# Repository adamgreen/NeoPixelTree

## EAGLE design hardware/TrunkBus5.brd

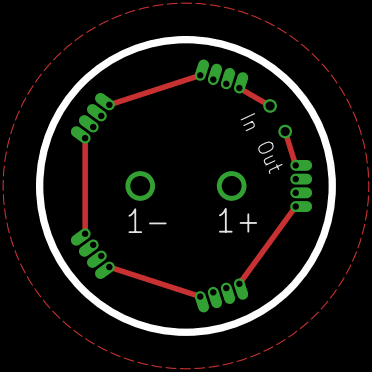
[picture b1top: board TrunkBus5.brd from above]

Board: 2 copper layers, 16.3 x 16.3 mm, 8 parts (0 on the bottom side), 8 nets.

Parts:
E$1: NEOPIXEL_TRUNK_2WIRE
E$5, E$6, E$7, E$8, E$10: NEOPIXEL_BRANCH_4WIRE
E$12, E$13: NEOPIXEL_26AWG_HOLE

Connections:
5V: E$1.P$1, E$5.P$1, E$6.P$1, E$7.P$1, E$8.P$1, E$10.P$1
GND: E$1.P$2, E$5.P$2, E$6.P$2, E$7.P$2, E$8.P$2, E$10.P$2
S$1: E$8.P$4, E$10.P$3
S$2: E$10.P$4, E$12.P$1
S$4: E$5.P$3, E$13.P$1
S$7: E$5.P$4, E$6.P$3
S$8: E$6.P$4, E$7.P$3
S$10: E$7.P$4, E$8.P$3

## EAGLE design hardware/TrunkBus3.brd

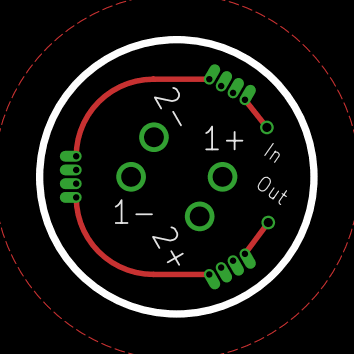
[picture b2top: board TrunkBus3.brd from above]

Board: 2 copper layers, 15.2 x 15.2 mm, 7 parts (0 on the bottom side), 6 nets.

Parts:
E$1, E$11: NEOPIXEL_TRUNK_2WIRE
E$2, E$6, E$8: NEOPIXEL_BRANCH_4WIRE
E$12, E$13: NEOPIXEL_26AWG_HOLE

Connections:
5V: E$1.P$1, E$2.P$1, E$6.P$1, E$8.P$1, E$11.P$1
GND: E$1.P$2, E$2.P$2, E$6.P$2, E$8.P$2, E$11.P$2
S$1: E$8.P$4, E$12.P$1
S$2: E$2.P$3, E$13.P$1
S$4: E$2.P$4, E$6.P$3
S$8: E$6.P$4, E$8.P$3

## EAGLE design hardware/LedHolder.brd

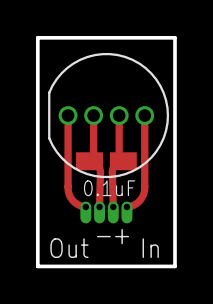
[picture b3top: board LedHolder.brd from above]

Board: 2 copper layers, 7.6 x 12.7 mm, 3 parts (0 on the bottom side), 4 nets.

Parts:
E$1: NEOPIXEL_5MM_TH
E$2: NEOPIXEL_BRANCH_4WIRE
E$3: 0.1uF; R0805W

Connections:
S$1: E$1.GROUND, E$2.P$1, E$3.1
S$2: E$1.5V, E$2.P$2, E$3.2
S$3: E$1.DATA_OUT, E$2.P$3
S$4: E$1.DATA_IN, E$2.P$4

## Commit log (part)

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2016-03-26 Add gcc4mbed as a submodule
    Using the working branch for now.
2016-03-27 GPDMA/SPI based updates of NeoPixels now working
    This commit is a checkpoint where the code is now able to use the
    GPDMA/SPI peripherals on the LPC17xx to automatically send out the
    required single wire waveform for the WS2812 based NeoPixels. The CPU
    is only used to convert the desired LED RGB values to a bitstream that
    can be sent out over the SPI MOSI pin to generate the expected WS2812
    waveform. This saves CPU cycles to be used for running animations.
2016-03-27 I don't need interlocked operations for this driver
    A previous implementation that I was working on needed to increment the
    frame counter in an interlocked fashion but this one doesn't.
2016-03-27 Remove some old debug code from main.cpp
    I had some leftover debug code in main.cpp where I was verifying that
    both front buffers were being updated correctly when client doesn't
    provide a new frame on very frame flip.
2016-03-27 Initial animation support
    This is the beginning of the various animations I want to try with this
    NeoPixel configuration.
    This commit includes:
    * I updated NeoPixel::set() method to take the length of the pPixel
    array passed in so that it can be verified against the m_ledCount
    that was set at construction time.
2016-03-27 Add twinkling animation
    I added an IPixelUpdate interface which the already existing Animation
    class now implements and so does the new TwinkleAnimation class. The
    main program then just maintains a IPixelUpdate pointer to the current
    animation engine and calls its updatePixels() method on each iteration
    through its main loop.
2016-03-27 Make animations templated on pixel count
    The animation classes no longer need to dynamically allocate pixel
    arrays. Now they take the pixel count as a template parameter and
    define an array within the class which is big enough to hold the
    pixels.
2016-03-29 Add back buffer support
    Previously the main thread would wait for the current front buffer to
    be sent and then it would fill that front buffer in while the other was
    being sent. This caused the CPU on average to wait half of a frame
    period each time it called NeoPixel::set().
    This new version has the main thread just filling in a separate
    back buffer. That back buffer will then be copied into the next front
2016-03-29 Add candle flicker animation
    This is the start of an animation that makes the LEDs flicker similar
    to how store bot LED candles flicker. The following webpage created by
    @cpldcpu provided a lot of inspiration for this animation:
    https://cpldcpu.wordpress.com/2016/01/05/reverse-engineering-a-real-candle/
    I also cleaned up some trailing whitespace in my logarithm table.
2016-04-01 Add some blue-white patterns as well
2016-04-01 Add schematic for current prototype
    This commit adds the Eagle schematic for the current 5 LED prototype
    that I am currently testing.
2016-04-02 Photos of tree prototype
2016-04-02 Add BSS138 N-Channel MOSFET documentation
2016-04-02 Initial README commit
2016-04-03 Fix error in README
    I had added a line break into the middle of a link by mistake.
2016-04-03 SPI bit layout comments were incorrect
    They were incorrectly indicating that a high bit to be sent to the
    WS2812 would be represented with 8 high pixels rather than the actual
    7 used in the driver.
2016-04-08 Add images
    The first is a clip from page 4 of the WS2812 LED driver datasheet. It
    shows the bit timings for the WS2812 serial protocol.
    The rest are hand drawn timing diagrams for my SPI implementation of
    the WS2812 serial protocol.
2016-04-08 Update README
    Added notes describing how I use SPI to generate WS2812 bit timings.
2016-04-08 Fix spelling error in README
2016-04-10 Add buffer notes to README
    I updated the README to have some notes about the transitions that the
    pixel data makes from 24-bit RGB arrays, to back buffer, to front
    buffer. It also touches on where and how GPDMA is utilized to reduce
    CPU load.
2016-05-07 Add LED holder PCB design
    I sent this design off to OSHPark to have 3 made to see how they work
    out. I made no schematic and just jumped to the layout since it was so
    simple.
2016-05-07 Upgrade to latest gcc4mbed release
2017-02-08 Add licenses
    Apache for source code and CC-BY-SA for hardware.
2017-02-08 LedHolder updates
    After getting back samples from the first version, I have decided to
    make a few changes for the next version:
    * Add an additional line to the top silkscreen to make the LED mounting
    orientation clearer as the LED silkscreen itself is a bit obfuscated
    by the holes themselves.
    * Expose more of the pad for the power supply lines. Currently the pad
2017-02-08 More LedHolder updates
    I switched the DataIn and DataOut connections to be through hole as
    well since the holes hold the wire in place to make it easier for
    soldering.
2018-02-03 Move NeoPixels to p5 from p11
    This makes room for using p11 as one of the rotary encoder pins as they
    need to be sequential LPC1768 pins.
2018-02-03 Initial encoder support
    I pulled existing LPC1768 quadature encoder code from my
    https://github.com/adamgreen/bb-8 project and then modified it to work
    with 3 rotary encoders (brightness, speed, and pattern) for this
    project.
    This is just an initial port. I will no doubt update it to make it more
    robust and more tolerant of bounce.
2018-02-04 Make rotary encoder code more robust
    This update was inspired by the following code from the Adafruit team:
    https://github.com/adafruit/Adafruit-Trinket-USB/blob/master/TrinketHidCombo/examples/TrinketVolumeKnob/TrinketVolumeKnob.ino
    It tracks the history of encoder state transitions that are seen
    between detent states. Once the encoder gets back to the detent state,
    the history can be queried to determine if it was more likely to have
    been rotated in a clockwise or counter clockwise direction.
2018-02-04 Read and clear encoder counts in 1 atomic operation
2018-02-08 Add rotary encoder button support
2018-02-09 Rewrite of rotary encoder filter
    I rewrote the rotary encoder code so that it first filters each encoder
    signal wire by only looking for pairs of clean HIGH (switch open)
    pulses and it then infers the length of the noisier LOW (switch closed)
    pulses. It returns the inferred LOW pulse and detected HIGH pulse back
    to the caller in a queue of length 2 containing the corresponding 2
    timestamped pulse descriptions.
2018-02-09 Add back in press support
    The previous filtering rewrite only supported sampling of rotation.
    This commit adds back in support for detecting shaft presses.
2018-03-02 Bump LED count up to 50
    The plan is to have 50 LEDs on the final tree so I bumped the count in
    the firmware to match. Previously it was set to 5 which meant that I
    couldn't test the 9 branches that I have on my current prototype.
2018-03-02 Create new LED holder PCB
    The new PCB is rectangular and will extend horizontally from the end of
    the branch wires. The LED will be bent at 90 degrees after being
    soldered into this board so that it lays horizontally as well. I will
    finalize the design once I have the flat cable in hand (currently on
    order).
2018-03-02 Start of 9 branch trunk bus bar layout
    This is the board which will be used to connect the lowest two layers
    of the tree (with 9 branches each) to the tree trunk. I will finalize
    the design once I have the flat cable in hand (currently on order).
2018-03-03 Ignore Eagle backup files
2018-03-07 Revision 1 of horizontal NeoPixel holder
    This is the PCB as ordered from OSHPark on 3/6/2018. The PCB is now
    routed and has updated text.
2018-03-07 Revision 1 of 9 branch trunk bus bar
    This is the PCB as ordered from OSHPark on 3/6/2018.
2018-03-23 Revision 2 of the latest boards
    Sent these revision 2 board off to OSHPark on March 23rd, 2018. I
    increased the drill sizes to accomodate the maximum of OSHPark's
    +/- 2.5mil drill tolerances. I also updated the 9 branch bus to
    fill top layer with 5V and move the DataIn/DataOut holes a bit to
    make room for the now larger ribbon cable holes.
2018-04-29 Revision 1 of 3,5,6,7, and 8 branch trunk bus bars
    These are the PCBs as ordered from OSHPark on 4/28/2018.
2018-10-02 Encoder code cleanup
    * Renamed MINIMUM_LOW_TIME to MINIMUM_HIGH_TIME to better describe its
    actual usage.
    * Cleaned up comments to better describe the *_LAST state transition
    macros.
2018-10-03 Enable animation selection encoder
    The leftmost rotary encoder can now be used to select the animations:
    * Pressing the encoder places it in demo mode (the default mode) which
    iterates through and plays each animation for a set amount of time.
    * Clockwise rotation exits demo mode and selects the next animation in
    the sequence. Stays at this animation until the user moves the
    encoder again.
2018-10-04 Fix /0 error in rgbToHsv()
    I introduced a divide by zero bug by not just returning when some of
    HSV components were detected to be 0. This bug didn't exist in the
    original code from stackoverflow.
2018-10-04 Enable brightness selection encoder
    The rightmost rotary encoder can now be used to control the brightness
    of the LEDs. The brightness setting is applied to all supported
    animations.
    Other changes in this commit include:
    * I now default all of the animations to use 50% brightness and this
    seems to be plenty bright enough.
2018-10-04 Enable speed selection encoder
    The middle rotary encoder can now be used to change the speed of the
    LED animations. Clockwise rotations speed up the animations and
    counterclockwise slow them down. The only animations not affected by
    this change are the solid ones (which don't animate) and the candle
    flicker animation.
2018-10-05 Add running lights animation
    Derived from code at the following link:
    https://www.tweaking4all.com/hardware/arduino/adruino-led-strip-effects/#LEDStripEffectRunningLights
2018-10-05 Add snow sparkle animation
    Modified the existing twinkle animation to support the snow sparkle
    animation from this link:
    https://www.tweaking4all.com/hardware/arduino/adruino-led-strip-effects/#LEDStripEffectSnowSparkle
2018-10-05 Add snowfall/meteor animation
    This is a port of the meteor animation found at this link:
    https://www.tweaking4all.com/hardware/arduino/adruino-led-strip-effects/#LEDStripEffectMeteorRain
    On the tree, when run from the top to the bottom, it kind of looks like
    snow falling down the tree.
2018-10-05 Slow down candle flicker animation
    The candle flicker animation was previously strobing too fast. This
    commit slows down the flicker and makes it a little more subtle.
2018-10-12 Add new animated GIF
    This new GIF shows the completed tree project flashing one of its many
    patterns.
2018-10-12 Update README
    Added a little bit of information about the final version of the
    project.
2018-11-27 Update hsvToRgb() to use some floating point
    I switched out an integer multiply with a floating point multiply so
    that a remainder of 42 (the maximum remainder) will be scaled to 255
    instead of 252. This allows pure green to be converted from RGB to HSV
    and back without any red being introduced.
